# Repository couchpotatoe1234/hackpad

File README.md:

# hackpad
A simple 4x4 macropad for my 3d designing on Onshape.
You can use this for the various tools in Onshape (sketch, extrude etc.) or you can change the keybinds to your own liking.
I designed this to improve my life using Onshape, not having to press all the keyboard shortcuts individually but having them all on one board.

(this is my overall model)

(these are my schematics)

(this is my PCB)

(this is my frame: link to Onshape:https://cad.onshape.com/documents/eaf805fe714e44a658f87d2d/w/abe58344c97c5e0e84d20075/e/9b6b4fc59104de51cb7dc8f9)

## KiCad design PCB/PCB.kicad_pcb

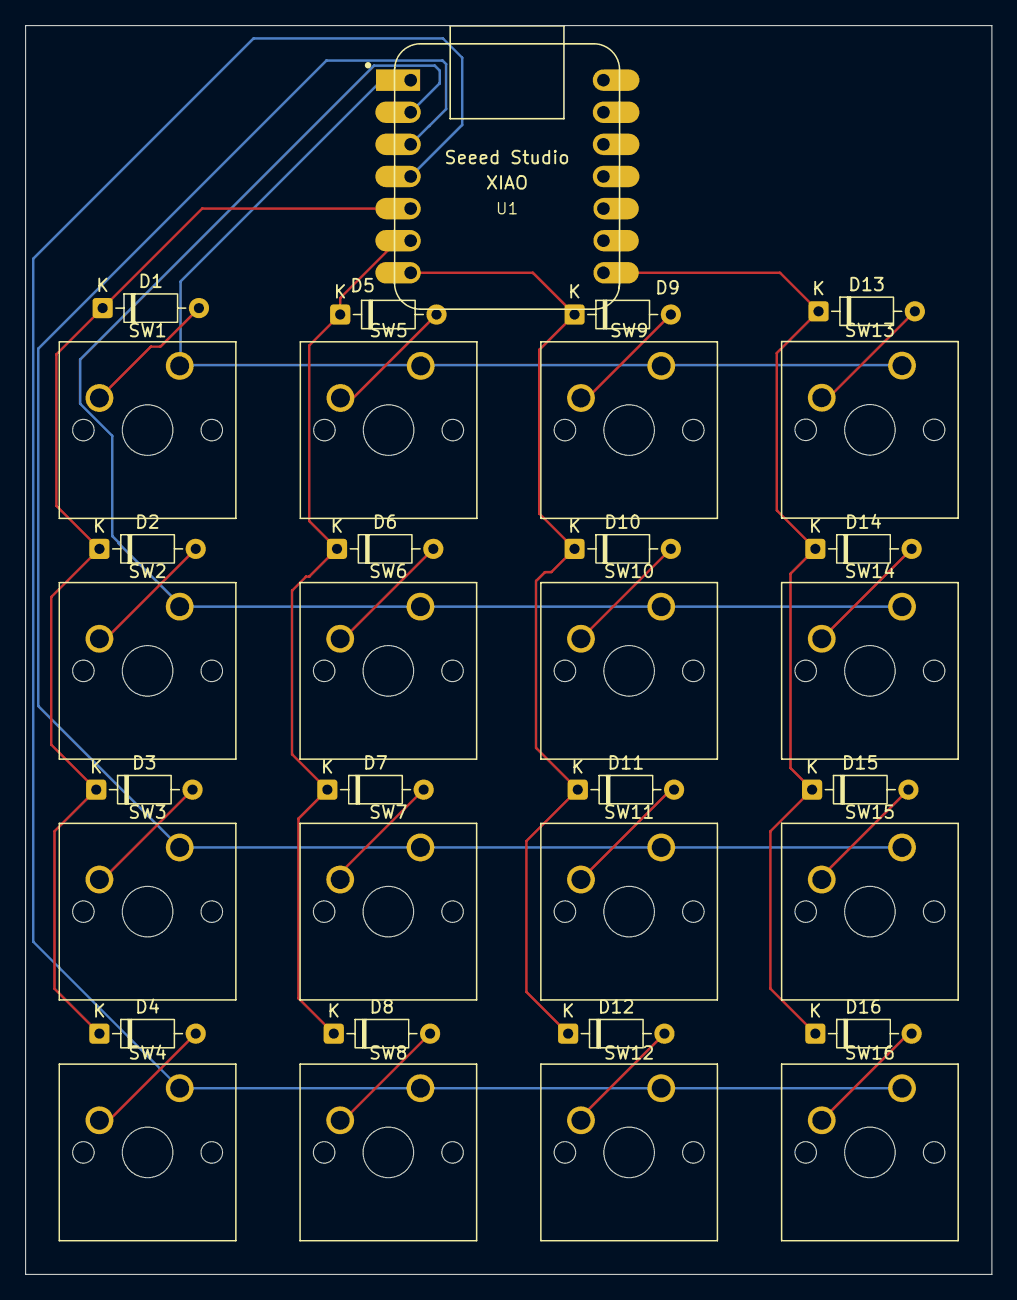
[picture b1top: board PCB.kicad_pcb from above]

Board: 2 copper layers, 76.5 x 98.8 mm, 33 parts (0 on the bottom side), 24 nets.

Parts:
D1, D2, D3, D4, D5, D6, D7, D8, D9, D10, D11, D12, D13, D14, D15, D16: 1N4148; D_DO-35_SOD27_P7.62mm_Horizontal
SW1, SW2, SW3, SW4, SW5, SW6, SW7, SW8, SW9, SW10, SW11, SW12, SW13, SW14, SW15, SW16: SW_Push; SW_Cherry_MX_1.00u_PCB
U1: MOUDLE-SEEEDUINO-XIAO; XIAO-Generic-Hybrid-14P-2.54-21X17.8MM

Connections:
Column 0: SW1.1, SW5.1, SW9.1, SW13.1, U1.1 (PA02_A0_D0)
Column 1: SW2.1, SW6.1, SW10.1, SW14.1, U1.2 (PA4_A1_D1)
Column 2: SW3.1, SW7.1, SW11.1, SW15.1, U1.3 (PA10_A2_D2)
Column 3: SW4.1, SW8.1, SW12.1, SW16.1, U1.4 (PA11_A3_D3)
unnamed: D1.2 (A), SW1.2
unnamed: D2.2 (A), SW2.2
unnamed: D3.2 (A), SW3.2
unnamed: D4.2 (A), SW4.2
unnamed: D5.2 (A), SW5.2
unnamed: D6.2 (A), SW6.2
unnamed: D7.2 (A), SW7.2
unnamed: D8.2 (A), SW8.2
unnamed: D9.2 (A), SW9.2
unnamed: D10.2 (A), SW10.2
unnamed: D11.2 (A), SW11.2
unnamed: D12.2 (A), SW12.2
unnamed: D13.2 (A), SW13.2
unnamed: D14.2 (A), SW14.2
unnamed: D15.2 (A), SW15.2
unnamed: D16.2 (A), SW16.2
Row 0: D1.1 (K), D2.1 (K), D3.1 (K), D4.1 (K), U1.5 (PA8_A4_D4_SDA)
Row 1: D5.1 (K), D6.1 (K), D7.1 (K), D8.1 (K), U1.6 (PA9_A5_D5_SCL)
Row 2: D9.1 (K), D10.1 (K), D11.1 (K), D12.1 (K), U1.7 (PB08_A6_D6_TX)
Row 3: D13.1 (K), D14.1 (K), D15.1 (K), D16.1 (K), U1.8 (PB09_A7_D7_RX)

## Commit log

2026-02-26 initial version
2026-02-26 second version
2026-02-28 third version
